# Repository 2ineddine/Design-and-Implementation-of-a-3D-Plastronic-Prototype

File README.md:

# 3D Plastronic Prototype with Arduino Control

## Project Overview
This project focuses on the design and implementation of an interactive electronic prototype that combines 3D plastronics with capacitive touch sensing. It consists of two functional 3D-printed plastic shells:

- A car shell equipped with programmable RGB LEDs
- A remote control shell featuring capacitive touch buttons using the MPR121 sensor

Both shells interface with an Arduino, enabling dynamic lighting effects triggered by user interactions through the touch interface.

## Objectives

- Design the electronic schematic and PCB layout using KiCad
- Integrate capacitive touch sensing via the MPR121 component
- Control RGB lighting effects using SK6812 addressable LEDs
- Manufacture two interactive shells using 3D printing: one for the car, one for the controller
- Demonstrate full system interaction through Arduino-based logic

## Components Used

| Component         | Description                          |
|-------------------|--------------------------------------|
| MPR121            | Capacitive touch sensor (I2C)        |
| SK6812 RGB LEDs   | Individually addressable LEDs        |
| Resistors         | 0805 and 1206 packages               |
| Capacitors        | 0805 decoupling capacitors           |
| Arduino           | Microcontroller (e.g., UNO or Nano)  |
| 3D-printed shells | Car and remote control enclosures    |

## Tools and Software

- **KiCad**: For schematic capture and PCB layout
- **Arduino IDE**: For programming and uploading firmware
- **3D design software**: e.g., OpenSCAD or Fusion 360 for shell modeling
- **3D printer**: For producing the physical enclosures

## Project Structure

```
/ProjectFolder
├── code/                    # Arduino sketches for controlling LEDs and input logic
├── the_car_shell_model/    # STEP file of the car shell
├── file_of_prototypes/     # 3D models of the electronic boards and routing
└── detailed_report/        # Complete technical report in PDF format
```

## Example Features

- Touch input on the remote triggers LED animations on the car shell
- Multiple lighting modes: blink, fade, rainbow
- Modular and adaptable Arduino code

## References

- MPR121 Datasheet – Adafruit Guide  
- KiCad Documentation – https://docs.kicad.org  
- SK6812 RGB LED Datasheet

## Author

- Project by: 2ineddine  
- Date: May 2024  
- Academic Level: Bachelor's in Electronics and Embedded Systems

## License

This project is intended for educational and demonstration purposes only.  
Feel free to reuse and adapt with proper credit.

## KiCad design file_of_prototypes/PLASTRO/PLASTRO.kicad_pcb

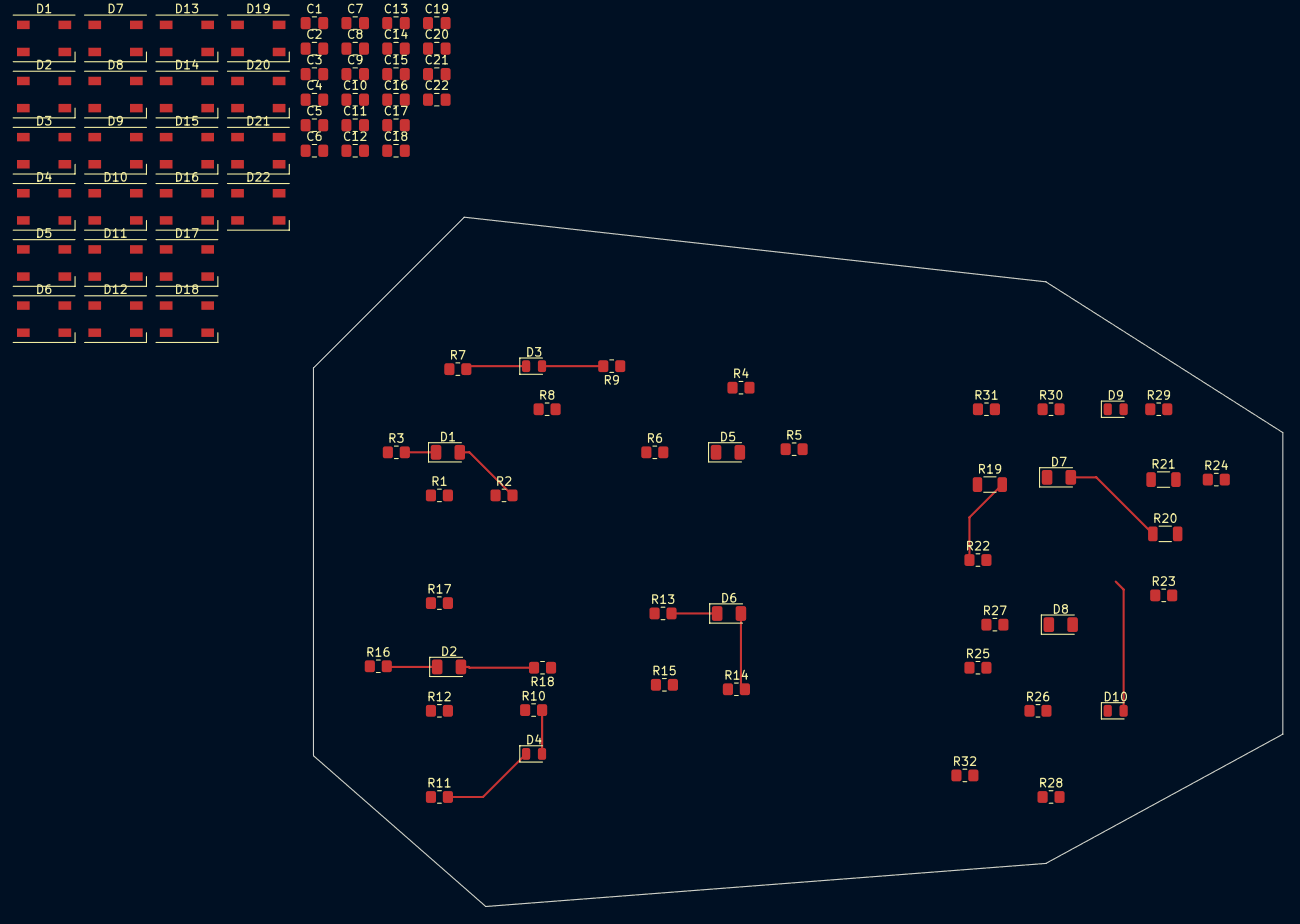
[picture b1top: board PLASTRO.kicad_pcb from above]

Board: 2 copper layers, 114.3 x 81.3 mm, 86 parts (0 on the bottom side), 40 nets.

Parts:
C1, C2, C3, C4, C5, C6, C7, C8, C9, C10, C11, C12, C13, C14, C15, C16, C17, C18, C19, C20, C21, C22: C; C_0805_2012Metric_Pad1.18x1.45mm_HandSolder
D1, D2, D3, D4, D5#2, D6#2, D7#2, D8, D9#2, D10#2, D11, D12, D13, D14, D15, D16, D17, D18, D19, D20, D21, D22: SK6812; LED_SK6812_PLCC4_5.0x5.0mm_P3.2mm
D1#2, D2#2, D5, D6, D7, D8#2: LED_RGBK; LED_1206_3216Metric
D3#2, D4#2, D9, D10: LED_RGBK; LED_0805_2012Metric
R1, R2, R3, R4, R5, R6, R7, R8, R9, R10, R11, R12, R13, R14, R15, R16, R17, R18, R22, R23, R24, R25, R26, R27, R28, R29, R30, R31, R32: R_US; R_0805_2012Metric_Pad1.20x1.40mm_HandSolder
R19, R20, R21: R_US; R_1206_3216Metric

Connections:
unnamed: D1.4 (DOUT), D21.2 (DIN)
unnamed: D1#2.2 (GA), R2.2
unnamed: D1#2.1 (RA), R3.2
unnamed: D2.4 (DOUT), D22.2 (DIN)
unnamed: D2#2.2 (GA), R18.2
unnamed: D2#2.1 (RA), R16.2
unnamed: D3.4 (DOUT), D6#2.2 (DIN)
unnamed: D3#2.2 (GA), R9.2
unnamed: D3#2.1 (RA), R7.2
unnamed: D4.4 (DOUT), D7#2.2 (DIN)
unnamed: D4#2.2 (GA), R10.2
unnamed: D4#2.1 (RA), R11.2
unnamed: D5#2.2 (DIN), D7#2.4 (DOUT)
unnamed: D5.2 (GA), R5.2
unnamed: D5.1 (RA), R6.2
unnamed: D6#2.4 (DOUT), D8.2 (DIN)
unnamed: D6.2 (GA), R14.2
unnamed: D6.1 (RA), R13.2
unnamed: D7.2 (GA), R20.1
unnamed: D7.1 (RA), R21.1
unnamed: D8#2.2 (GA), R26.1
unnamed: D8#2.1 (RA), R27.1
unnamed: R28.1, R32.2
unnamed: D9.1 (RA), R30.2
unnamed: D9#2.2 (DIN), D10#2.4 (DOUT)
unnamed: D9.2 (GA), D10.2 (GA), R29.1
unnamed: D10.1 (RA), R30.1, R31.1
unnamed: D11.2 (DIN), D12.4 (DOUT)
unnamed: D11.4 (DOUT), D13.2 (DIN)
unnamed: D9#2.4 (DOUT), D12.2 (DIN)
unnamed: D13.4 (DOUT), D16.2 (DIN)
unnamed: D14.2 (DIN), D16.4 (DOUT)
unnamed: D14.4 (DOUT), D15.2 (DIN)
unnamed: D17.4 (DOUT), D20.2 (DIN)
unnamed: D18.4 (DOUT), D19.2 (DIN)
unnamed: R19.2, R22.1
unnamed: R20.2, R23.1
unnamed: R21.2, R24.1
VCC: C1.1, C2.1, C3.1, C4.1, C5.1, C6.1, C7.1, C8.1, C9.1, C10.1, C11.1, C12.1, C13.1, C14.1, C15.1, C16.1, C17.1, C18.1, C19.1, C20.1, C21.1, C22.1, D1.3 (VDD), D2.3 (VDD), D3.3 (VDD), D4.3 (VDD), D5#2.3 (VDD), D6#2.3 (VDD), D7#2.3 (VDD), D8.3 (VDD), D9#2.3 (VDD), D10#2.3 (VDD), D11.3 (VDD), D12.3 (VDD), D13.3 (VDD), D14.3 (VDD), D15.3 (VDD), D16.3 (VDD), D17.3 (VDD), D18.3 (VDD), D19.3 (VDD), D20.3 (VDD), D21.3 (VDD), D22.3 (VDD)
gnd: C1.2, C2.2, C3.2, C4.2, C5.2, C6.2, C7.2, C8.2, C9.2, C10.2, C11.2, C12.2, C13.2, C14.2, C15.2, C16.2, C17.2, C18.2, C19.2, C20.2, C21.2, C22.2, D1.1 (VSS), D2.1 (VSS), D3.1 (VSS), D4.1 (VSS), D5#2.1 (VSS), D6#2.1 (VSS), D7#2.1 (VSS), D8.1 (VSS), D9#2.1 (VSS), D10#2.1 (VSS), D11.1 (VSS), D12.1 (VSS), D13.1 (VSS), D14.1 (VSS), D15.1 (VSS), D16.1 (VSS), D17.1 (VSS), D18.1 (VSS), D19.1 (VSS), D20.1 (VSS), D21.1 (VSS), D22.1 (VSS)

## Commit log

2025-05-15 KiCad files
2025-05-15 project report
2025-05-15 lighting effect code
2025-05-15 Solidworks files
